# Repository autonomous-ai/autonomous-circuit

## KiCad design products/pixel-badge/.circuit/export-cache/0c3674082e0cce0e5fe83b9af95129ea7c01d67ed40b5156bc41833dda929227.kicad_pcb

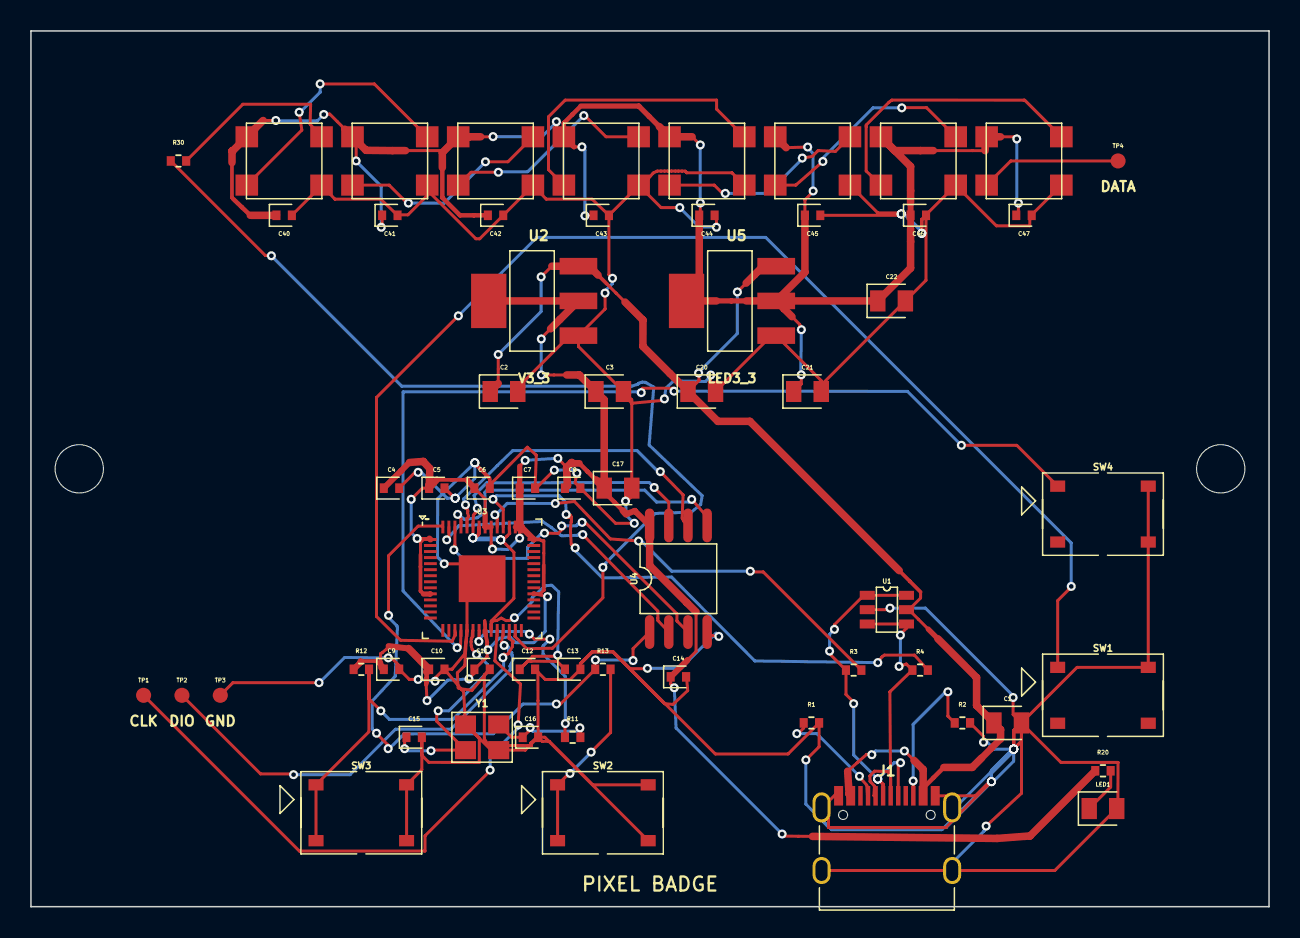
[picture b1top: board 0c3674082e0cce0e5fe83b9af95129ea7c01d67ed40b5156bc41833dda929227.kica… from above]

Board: 2 copper layers, 82.0 x 58.0 mm, 61 parts (0 on the bottom side), 37 nets.

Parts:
C1, C2, C3, C17, C20, C21, C22: 10uF; capacitor_cap0805
C4, C5, C6, C7, C8, C9, C10, C11, C13, C14, C40, C41, C42, C43, C44, C45, C46, C47: 100nF; capacitor_cap0402
C12: 1uF; capacitor_cap0402
C15, C16: 15pF; capacitor_cap0402
D10, D11, D12, D13, D14, D15, D16, D17: WS2812B-B/T; WS2812B-B_T
J1: J1; TYPE-C-31-M-12
LED1: LED; led_0805_color(green)
R1, R2: 5.1kΩ; resistor_res0402
R3, R4: 27Ω; resistor_res0402
R11, R13, R20: 1kΩ; resistor_res0402
R12: 10kΩ; resistor_res0402
R30: 330Ω; resistor_res0402
SW1: SW1; push_button_dfn4_p3.6998mm_w7mm_pw0.75mm
SW2: SW2; push_button_dfn4_p3.6998mm_w7mm_pw0.75mm
SW3: SW3; push_button_dfn4_p3.6998mm_w7mm_pw0.75mm
SW4: SW4; push_button_dfn4_p3.6998mm_w7mm_pw0.75mm
TP1: TP1; test_point_smtpad_circle_d1
TP2: TP2; test_point_smtpad_circle_d1
TP3: TP3; test_point_smtpad_circle_d1
TP4: TP4; test_point_smtpad_circle_d1
U1: USBLC6-2SC6
U2, U5: AMS1117-3.3
U3: RP2040
U4: W25Q128JVSIQ
Y1: Y1; crystal_crystal

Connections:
.J1 > .CC1 to .R1 > .pin1: J1.6, R1.1
.J1 > .CC2 to .R2 > .pin1: J1.12, R2.1
.R11 > .pin2 to .Y1 > .pin3: C16.1, R11.2, Y1.3
.R20 > .pin2 to .LED1 > .anode: LED1.1, R20.2
.U3 > .XOUT to .R11 > .pin1: R11.1, U3.21
.U4 > .CLK to .U3 > .QSPI_SCLK: U3.52, U4.6
.U4 > .CS to .U3 > .QSPI_SS: R13.1, U3.56, U4.1
.U4 > .IO0 to .U3 > .QSPI_SD0: U3.53, U4.5
.U4 > .IO1 to .U3 > .QSPI_SD1: U3.55, U4.2
.U4 > .IO2 to .U3 > .QSPI_SD2: U3.54, U4.3
.U4 > .IO3 to .U3 > .QSPI_SD3: U3.51, U4.7
.Y1 > .pin1 to .U3 > .XIN: C15.1, U3.20, Y1.1
BOOTSEL_SW: R13.2, SW2.1, SW2.2
BTN_BRIGHT: SW4.1, U3.18
BTN_MODE: SW1.1, U3.17
DVDD: C12.1, C13.1, U3.23, U3.45, U3.50
GND: C1.2, C2.2, C3.2, C4.2, C5.2, C6.2, C7.2, C8.2, C9.2, C10.2, C11.2, C12.2, C13.2, C14.2, C15.2, C16.2, C17.2, C20.2, C21.2, C22.2, C40.2, C41.2, C42.2, C43.2, C44.2, C45.2, C46.2, C47.2, D10.3, D11.3, D12.3, D13.3, D14.3, D15.3, D16.3, D17.3, J1.1, J1.2, J1.3, J1.4, J1.13, J1.14, LED1.2, R1.2, R2.2, SW1.4, SW2.3, SW2.4, SW3.3, SW3.4, SW4.4, TP3.1, U1.2, U2.1, U3.19, U3.57, U4.4, U5.1, Y1.2, Y1.4
LED_DATA: R30.1, U3.27
PX_10_DIN: D10.4, R30.2
PX_11_DIN: D10.2, D11.4
PX_12_DIN: D11.2, D12.4
PX_13_DIN: D12.2, D13.4
PX_14_DIN: D13.2, D14.4
PX_15_DIN: D14.2, D15.4
PX_16_DIN: D15.2, D16.4
PX_17_DIN: D16.2, D17.4
PX_18_DIN: D17.2, TP4.1
RUN_SW: R12.2, SW3.1, SW3.2, U3.26
SWCLK: TP1.1, U3.24
SWD: TP2.1, U3.25
USB_DM: R4.2, U3.46
USB_DM_CONN: J1.7, J1.9, R4.1, U1.3, U1.4
USB_DP: R3.2, U3.47
USB_DP_CONN: J1.8, J1.10, R3.1, U1.1, U1.6
V3_3: C3.1, C4.1, C5.1, C6.1, C7.1, C8.1, C9.1, C10.1, C11.1, C14.1, C17.1, R12.1, R20.1, U2.2, U2.4, U3.1, U3.10, U3.22, U3.33, U3.42, U3.43, U3.44, U3.48, U3.49, U4.8
V3_3_LED: C21.1, C22.1, C40.1, C41.1, C42.1, C43.1, C44.1, C45.1, C46.1, C47.1, D10.1, D11.1, D12.1, D13.1, D14.1, D15.1, D16.1, D17.1, U5.2, U5.4
V5: C1.1, C2.1, C20.1, J1.15, J1.16, U1.5, U2.3, U5.3
